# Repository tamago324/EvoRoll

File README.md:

# EvoRoll

左側を haqua34、右側を EvoRoll として使うことを想定している

> NOTE: KiCad 7 を使用しています

## [v1](v1/README.md)

## [v2](v2/README.md)

## [v3](v3/README.md)

## [v4](v4/README.md)

## LICENSE

<br />この 作品 は <a rel="license" href="http://creativecommons.org/licenses/by-nc/4.0/">クリエイティブ・コモンズ 表示 - 非営利 4.0 国際 ライセンス</a>の下に提供されています。

> 表示 — あなたは 適切なクレジットを表示し、ライセンスへのリンクを提供し、変更があったらその旨を示さなければなりません。これらは合理的であればどのような方法で行っても構いませんが、許諾者があなたやあなたの利用行為を支持していると示唆するような方法は除きます。
>
> 非営利 — あなたは営利目的でこの資料を利用してはなりません。

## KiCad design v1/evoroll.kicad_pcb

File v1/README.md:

# EvoRoll v1

左側を haqua34、右側を EvoRoll として使うことを想定している

> NOTE: KiCad 7 を使用しています

## 特徴

* GameBall のボールを使用したトラックボール付きキーボード
* マウスキーが独立している
* [monkeypad/pmw3360-breakout](https://github.com/monkeypad/pmw3360-breakout) を使用

## 部品

|部品|リンク|備考|
|---|---|---|
|PMW3360ブレークアウトボード|[monkeypad/pmw3360-breakout](https://github.com/monkeypad/pmw3360-breakout)|Booth で購入したら、ピンヘッダーもついていたけど、おそらく[これ](https://www.hirosugi-net.co.jp/shop/c/c12103211/)|
|ピンソケット 8ピン|https://www.hirosugi-net.co.jp/shop/c/c12111211/|FSR-41085-08 / 8.5mmのものを使用する|
|スペーサー M2 5mm|https://www.hirosugi-net.co.jp/shop/c/c10141012/|トッププレートとボトムプレートを止めるために使用する|
|ねじ M2 3mm|https://wilco.jp/products/F/FX-EB.html#page3|トッププレートとボトムプレートを止めるために使用する|
|タッピングネジ M2 8mm|https://wilco.jp/products/F/FPP-N.html|FPP-0000N / ボトムプレートとボールケースを止めるために使用する。JLCPCBのレジンに使えるタッピングネジ|
|RP2040-Zero|||
|ダイオード|||
|chocソケット|||
|TRRSソケット|||

### ボールケース関連

ボールケースは [trackmacro](https://github.com/tamago324/trackmacro/tree/main/stl) のケースを使用している

|部品|リンク|備考|
|---|---|---|
|ベアリング|https://amzn.asia/d/8OED4Yl|DDL-520ZZW52 / 内径2mm、外形5mm、幅2.5mm|
|ねじ M2 8mm||なべ小ねじならなんでもOK (頭径3.5mm、高さ1.3)|
|ナット M2||1種のナットを使っている|
|磁石 3x2mm|https://amzn.asia/d/gBrgy0N|ボールケースの上下に瞬間接着剤 (アロンアルフア EXTRA 速効多用途) でつけている|

## 3Dプリント

* JLCPCB の3Dプリントを使う想定
* stl 内の stl ファイルを SLA(Resin) で発注する

## ファームウェア

https://github.com/tamago324/keyboard-firmwares/tree/master/keyboards/evoroll

## LICENSE

<br />この 作品 は <a rel="license" href="http://creativecommons.org/licenses/by-nc/4.0/">クリエイティブ・コモンズ 表示 - 非営利 4.0 国際 ライセンス</a>の下に提供されています。

> 表示 — あなたは 適切なクレジットを表示し、ライセンスへのリンクを提供し、変更があったらその旨を示さなければなりません。これらは合理的であればどのような方法で行っても構いませんが、許諾者があなたやあなたの利用行為を支持していると示唆するような方法は除きます。
>
> 非営利 — あなたは営利目的でこの資料を利用してはなりません。

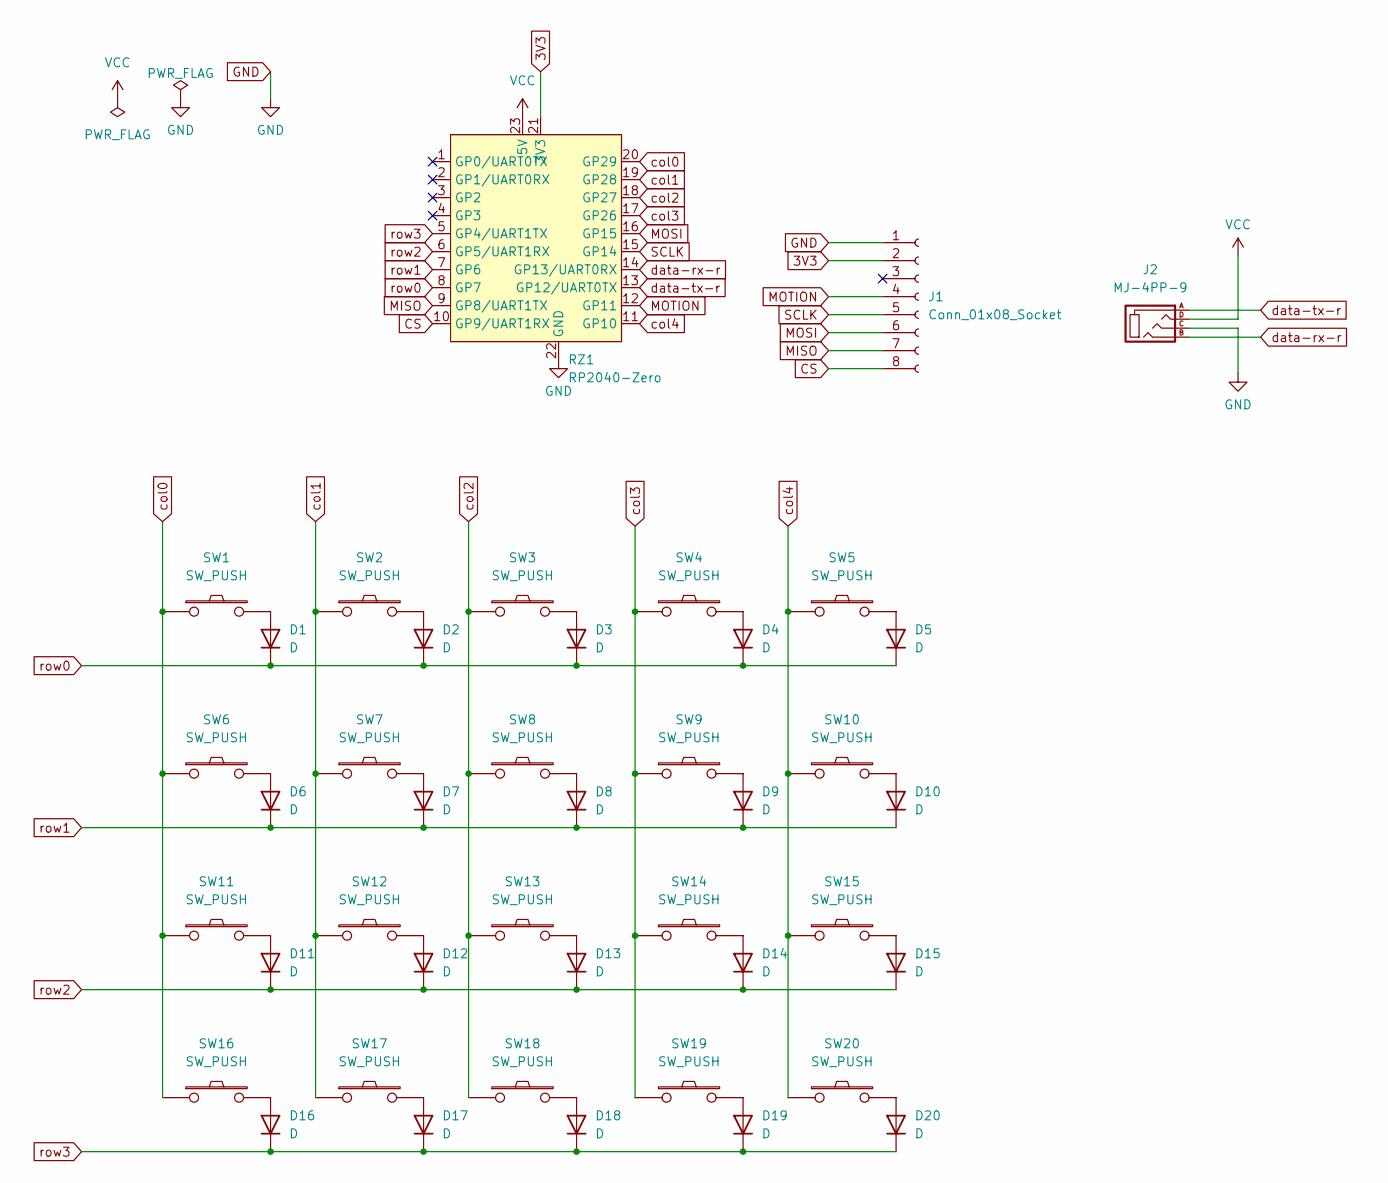
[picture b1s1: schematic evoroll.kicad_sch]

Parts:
D1, D2, D3, D4, D5, D6, D7, D8, D9, D10, D11, D12, D13, D14, D15, D16, D17, D18, D19, D20: D; D3_SMD
J1: Conn_01x08_Socket; PinSocket_1x08_P2.54mm
J2: MJ-4PP-9
RZ1: RP2040-Zero
SW1, SW2, SW3, SW4, SW5, SW6, SW7, SW8, SW9, SW10, SW11, SW12, SW13, SW14, SW15, SW16, SW17, SW18, SW19, SW20: SW_PUSH; Kailh_socket_PG1350

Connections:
3V3: J1.2, RZ1.21 (3V3)
CS: J1.8, RZ1.10 (GP9/UART1RX)
GND: J1.1, J2.C, RZ1.22 (GND)
MISO: J1.7, RZ1.9 (GP8/UART1TX)
MOSI: J1.6, RZ1.16 (GP15)
MOTION: J1.4, RZ1.12 (GP11)
unnamed: D1.2 (A), SW1.2
unnamed: D2.2 (A), SW2.2
unnamed: D3.2 (A), SW3.2
unnamed: D4.2 (A), SW4.2
unnamed: D5.2 (A), SW5.2
unnamed: D6.2 (A), SW6.2
unnamed: D7.2 (A), SW7.2
unnamed: D8.2 (A), SW8.2
unnamed: D9.2 (A), SW9.2
unnamed: D10.2 (A), SW10.2
unnamed: D11.2 (A), SW11.2
unnamed: D12.2 (A), SW12.2
unnamed: D13.2 (A), SW13.2
unnamed: D14.2 (A), SW14.2
unnamed: D15.2 (A), SW15.2
unnamed: D16.2 (A), SW16.2
unnamed: D17.2 (A), SW17.2
unnamed: D18.2 (A), SW18.2
unnamed: D19.2 (A), SW19.2
unnamed: D20.2 (A), SW20.2
SCLK: J1.5, RZ1.15 (GP14)
VCC: J2.D, RZ1.23 (5V)
col0: RZ1.20 (GP29), SW1.1, SW6.1, SW11.1, SW16.1
col1: RZ1.19 (GP28), SW2.1, SW7.1, SW12.1, SW17.1
col2: RZ1.18 (GP27), SW3.1, SW8.1, SW13.1, SW18.1
col3: RZ1.17 (GP26), SW4.1, SW9.1, SW14.1, SW19.1
col4: RZ1.11 (GP10), SW5.1, SW10.1, SW15.1, SW20.1
data-rx-r: J2.B, RZ1.14 (GP13/UART0RX)
data-tx-r: J2.A, RZ1.13 (GP12/UART0TX)
row0: D1.1 (K), D2.1 (K), D3.1 (K), D4.1 (K), D5.1 (K), RZ1.8 (GP7)
row1: D6.1 (K), D7.1 (K), D8.1 (K), D9.1 (K), D10.1 (K), RZ1.7 (GP6)
row2: D11.1 (K), D12.1 (K), D13.1 (K), D14.1 (K), D15.1 (K), RZ1.6 (GP5/UART1RX)
row3: D16.1 (K), D17.1 (K), D18.1 (K), D19.1 (K), D20.1 (K), RZ1.5 (GP4/UART1TX)

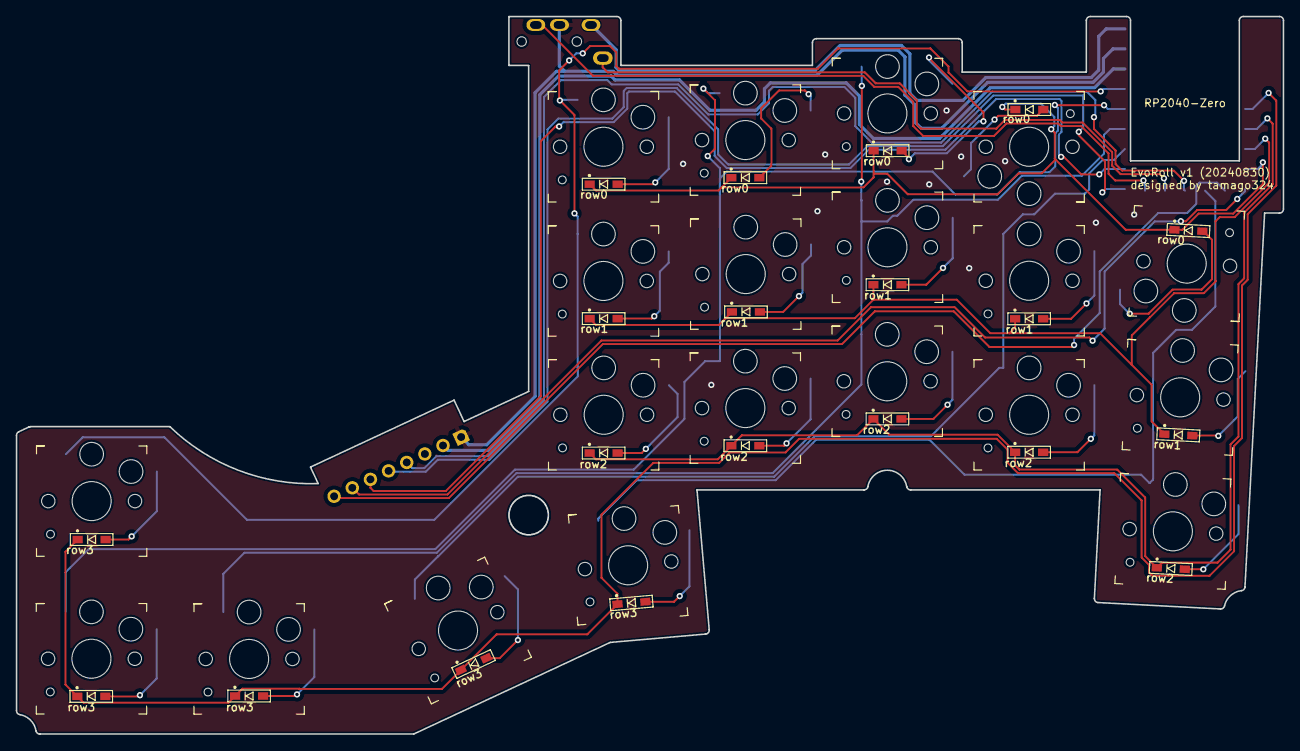
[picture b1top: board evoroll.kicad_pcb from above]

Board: 2 copper layers, 160.7 x 91.0 mm, 44 parts (0 on the bottom side), 39 nets.

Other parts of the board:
Ref**: Val**; M2_HOLE_v2_5mm

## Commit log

2024-09-05 init
2024-09-05 ファームウェアの場所を追加
2024-10-05 v1 フォルダに移動
2024-10-05 README に v1 と v2 へのリンクを作成
2024-10-14 v2 追加
2024-10-31 v3 追加
2024-12-01 v4 追加

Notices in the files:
README.md:
LICENSE:
CC BY-NC 4.0
